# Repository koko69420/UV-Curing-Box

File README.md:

# UV PCB Curing Box

A dedicated, safety-interlocked UV exposure and resin curing chamber controller powered by the ultra-low-cost WCH CH32V003 RISC-V microcontroller, featuring a 4x4 matrix keypad, a 4-digit TM1637 7-segment display, software PWM brightness control, and custom KiCad hardware.

---

## Features

- **RISC-V Microcontroller Core**:
  - Implemented on the WCH CH32V003A4M6 (QingKe 32-bit RISC-V2A core @ 48 MHz, 16 KB Flash, 2 KB SRAM).
  - Built with the PlatformIO Community CH32V Arduino core (`ch32v003fun` HAL).
- **Fail-Safe UV Safety Interlocking**:
  - The high-power UV LED MOSFET (pin A2) is strictly energized ONLY during the active `RUNNING` state.
  - Transitions to `BOOT`, `IDLE`, `READY`, `PAUSED`, or `FINISHED` instantly and continuously force the gate LOW.
- **Dual Timing Modes**:
  - **Timer Mode**: Countdown timer with customizable duration (capped at 8:00 minutes) and automated shutoff.
  - **Stopwatch Mode**: Elapsed time counter with live LED toggling.
- **Fast Presets & Matrix Keypad Input**:
  - 4x4 matrix keypad interface for direct numeric entry, pause/resume, and reset.
  - One-touch curing duration presets:
    - **A**: 1:00 min
    - **B**: 1:30 min
    - **C**: 2:00 min
    - **D**: 3:00 min
  - On-the-fly cycle extension (`#` button adds +5 seconds, clamped to 8:00).
- **PWM Exposure Brightness Regulation**:
  - 50 Hz sampled software PWM (0–100%) designed to eliminate flicker and ensure accurate optical dose delivery.
  - Dedicated on-screen brightness tuning menu (`b 0` to `b100`).
- **Telemetry & Status Display**:
  - TM1637 4-digit 7-segment display showing MM:SS with blinking colon indicators during exposure.
- **Custom Hardware & PCB**:
  - Designed in KiCad with full schematics, PCB routing, 3D step models, and vector silkscreens.

---

## Hardware Specification

### Components & Microcontroller
- **MCU**: WCH CH32V003A4M6 (TSSOP-20).
- **Display**: TM1637 4-digit 0.36" / 0.56" 7-segment clock display module.
- **Keypad**: 4x4 tactile matrix keypad.
- **Switching MOSFET**: N-Channel Power MOSFET (low-side switch on A2 driving 395nm/405nm UV LED arrays).
- **Power Input**: 12V DC input for LED strings with onboard 5V / 3.3V LDO regulation for logic.

---

## Hardware Prototype & Visual Design

### Live Hardware Prototype
Below is the operational controller prototype executing a countdown exposure on the TM1637 4-digit display:

### Electrical Schematic

### PCB Board Layout & Copper Routing

| Complete Board Layout | Top Copper Layer (`F_Cu`) | Bottom Copper Layer (`B_Cu`) |
| :---: | :---: | :---: |
|  |  |  |

---

### Pinout Mapping

| Function | Pin Name | Direction | Description |
| :--- | :--- | :--- | :--- |
| **Keypad Row 1** | C1 | Output | Matrix row scan line 1 |
| **Keypad Row 2** | C2 | Output | Matrix row scan line 2 |
| **Keypad Row 3** | C3 | Output | Matrix row scan line 3 |
| **Keypad Row 4** | C4 | Output | Matrix row scan line 4 |
| **Keypad Col 1** | C6 | Input (Pullup)| Matrix column sense line 1 |
| **Keypad Col 2** | C7 | Input (Pullup)| Matrix column sense line 2 |
| **Keypad Col 3** | D4 | Input (Pullup)| Matrix column sense line 3 |
| **Keypad Col 4** | D5 | Input (Pullup)| Matrix column sense line 4 |
| **TM1637 CLK** | D6 | Output | Display serial clock |
| **TM1637 DIO** | A1 | Bidirectional| Display serial data line |
| **UV MOSFET Gate**| A2 | Output | Low-side power gate driver (PWM) |

---

## State Machine

```mermaid
stateDiagram-v2
    [*] --> BOOT
    BOOT --> IDLE: Initialization Complete
    IDLE --> READY: Digit Entry or Preset (A-D)
    READY --> RUNNING: Press '#' (Start)
    RUNNING --> PAUSED: Press '*' (Pause)
    PAUSED --> RUNNING: Press '#' (Resume)
    PAUSED --> IDLE: Press '*' (Reset to Zero)
    RUNNING --> FINISHED: Time Reaches 0:00 (Timer) or 8:00 (Stopwatch)
    FINISHED --> IDLE: 5s Auto-timeout or Any Key
```

---

## Project Structure

```text
UV-Curing-Box/
├── Programs/                         # PlatformIO firmware project
│   ├── platformio.ini                # CH32V003 target configuration
│   └── src/
│       └── main.cpp                  # Complete non-blocking state machine & firmware
├── Schematic.pdf                     # Schematic diagram export
├── UV_curing_box.kicad_sch           # KiCad schematic
├── UV_curing_box.kicad_pcb           # KiCad PCB board layout
├── MCU_WCH_CH32V003xxx6.kicad_sym   # Custom CH32V003 symbol library
├── led_string.kicad_sch              # UV LED array layout
├── UV_curing_box.svg                 # Scalable vector graphics board plot
├── .gitignore                        # Git ignore rules
└── README.md                         # Project documentation
```

---

## Firmware Compilation & Flashing

### Using PlatformIO (VS Code / CLI)
1. Install [PlatformIO Core](https://platformio.org/) and the Community CH32V platform:
   ```bash
   cd Programs
   pio run
   ```
2. Connect a **WCH-LinkE** programmer to the single-wire debug interface (SWDIO on pin D1, GND, 3V3).
3. Upload firmware:
   ```bash
   pio run --target upload
   ```

---

## License

Open hardware and embedded firmware. All rights reserved by the author.

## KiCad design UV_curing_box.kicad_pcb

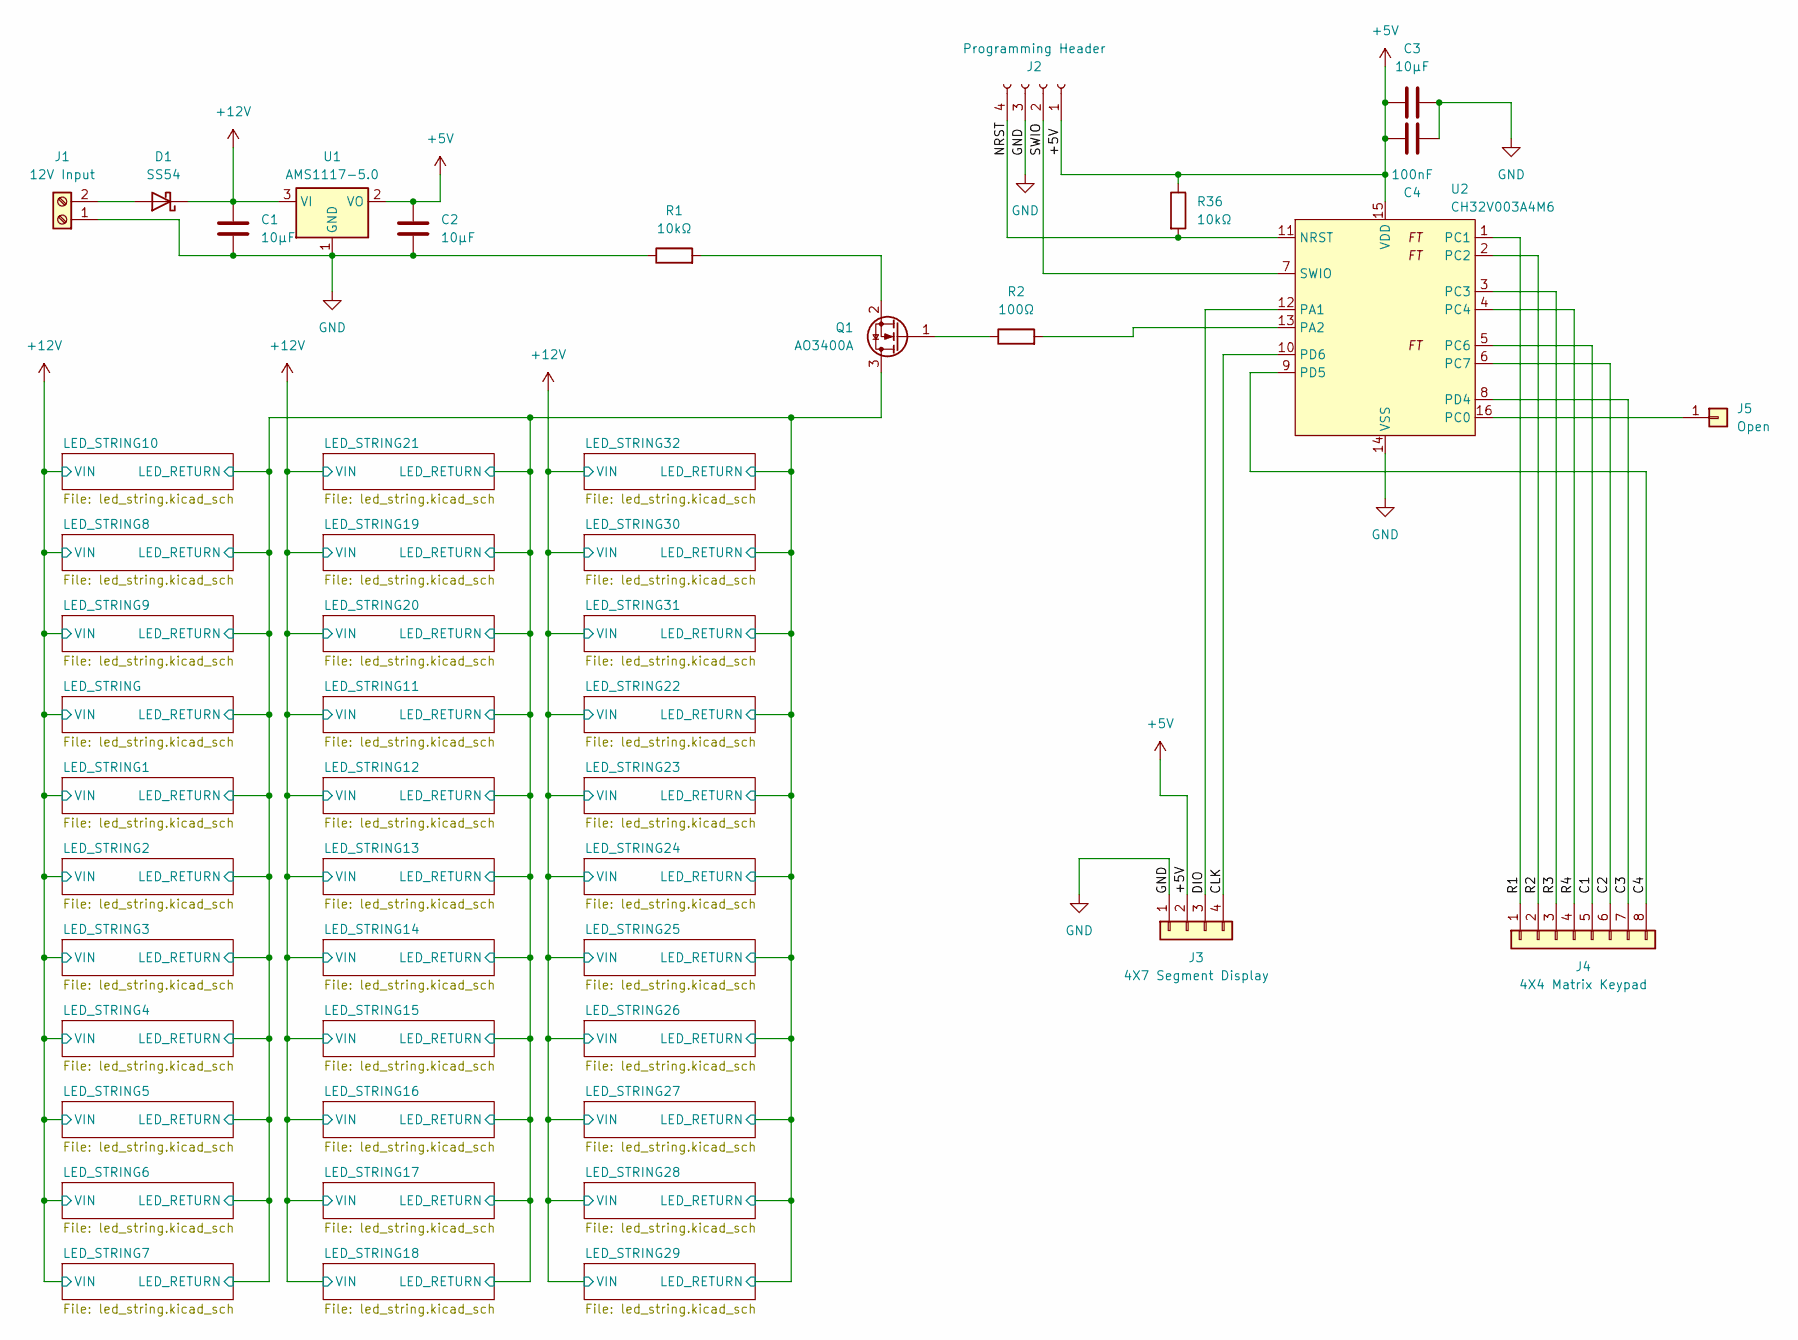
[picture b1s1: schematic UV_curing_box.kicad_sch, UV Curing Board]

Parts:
C1, C2, C3: 10µF; C_1206_3216Metric_Pad1.33x1.80mm_HandSolder
C4: 100nF; C_1206_3216Metric_Pad1.33x1.80mm_HandSolder
D1: SS54; D_SMA_Handsoldering
J1: 12V Input; TerminalBlock_MaiXu_MX126-5.0-02P_1x02_P5.00mm
J2: Programming Header; PinSocket_1x04_P2.54mm_Vertical
J3: 4X7 Segment Display; smd_conn_1x04_2.54
J4: 4X4 Matrix Keypad; smd_conn_1x08_2.54
J5: Open; SolderWirePad_1x01_SMD_1.5x3mm
Q1: AO3400A; SOT-23
R1, R36: 10kΩ; R_1206_3216Metric_Pad1.30x1.75mm_HandSolder
R2: 100Ω; R_1206_3216Metric_Pad1.30x1.75mm_HandSolder
U1: AMS1117-5.0; SOT-223-3_TabPin2
U2: CH32V003A4M6; SO-16_3.9x9.9mm_P1.27mm

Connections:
+5V: C2.1, C3.1, C4.1, J2.1, J3.2, R36.1, U1.2 (VO), U2.15 (VDD)
+12V: C1.1, D1.1 (K), U1.3 (VI); also elsewhere on the board
/C1: J4.5, U2.5 (PC6)
/C2: J4.6, U2.6 (PC7)
/C3: J4.7, U2.8 (PD4)
/C4: J4.8, U2.9 (UART_TX)
/CLK: J3.4, U2.10 (UART_RX)
/DIO: J3.3, U2.12 (OSCI)
/LED_STRING/LED_RETURN: Q1.3 (D); also elsewhere on the board
/NRST: J2.4, R36.2, U2.11 (NRST)
/R1: J4.1, U2.1 (PC1)
/R2: J4.2, U2.2 (PC2)
/R3: J4.3, U2.3 (PC3)
/R4: J4.4, U2.4 (PC4)
/SWIO: J2.2, U2.7 (SWIO)
GND: C1.2, C2.2, C3.2, C4.2, J1.1, J2.3, J3.1, R1.1, U1.1 (GND), U2.14 (VSS)
unnamed: D1.2 (A), J1.2
unnamed: J5.1, U2.16 (PC0)
unnamed: Q1.1 (G), R2.1
unnamed: Q1.2 (S), R1.2
unnamed: R2.2, U2.13 (OSCO)

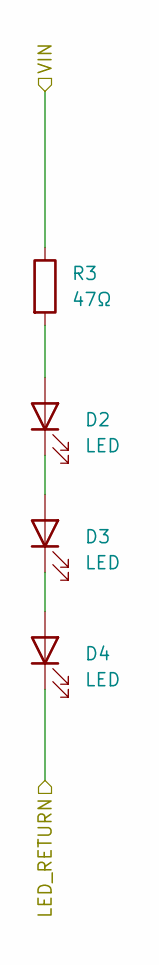
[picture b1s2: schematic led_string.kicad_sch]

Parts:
D2, D3, D4: LED; LED_PLCC_2835_Handsoldering
R3: 47Ω; R_1206_3216Metric_Pad1.30x1.75mm_HandSolder

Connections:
+12V: R3.1; also elsewhere on the board
/LED_STRING/LED_RETURN: D4.1 (K); also elsewhere on the board
unnamed: D2.2 (A), R3.2
unnamed: D2.1 (K), D3.2 (A)
unnamed: D3.1 (K), D4.2 (A)

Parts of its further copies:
D5, D6, D7, D8, D9, D10, D11, D12, D13, D14, D15, D16, D17, D18, D19, D20, D21, D22, D23, D24, D25, D26, D27, D28, D29, D30, D31, D32, D33, D34, D35, D36, D37, D38, D39, D40, D41, D42, D43, D44, D45, D46, D47, D48, D49, D50, D51, D52, D53, D54, D55, D56, D57, D58, D59, D60, D61, D62, D63, D64, D65, D66, D67, D68, D69, D70, D71, D72, D73, D74, D75, D76, D77, D78, D79, D80, D81, D82, D83, D84, D85, D86, D87, D88, D89, D90, D91, D92, D93, D94, D95, D96, D97, D98, D99, D100: LED; LED_PLCC_2835_Handsoldering
R4, R5, R6, R7, R8, R9, R10, R11, R12, R13, R14, R15, R16, R17, R18, R19, R20, R21, R22, R23, R24, R25, R26, R27, R28, R29, R30, R31, R32, R33, R34, R35: 47Ω; R_1206_3216Metric_Pad1.30x1.75mm_HandSolder

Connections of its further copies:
+12V: R4.1, R5.1, R6.1, R7.1, R8.1, R9.1, R10.1, R11.1, R12.1, R13.1, R14.1, R15.1, R16.1, R17.1, R18.1, R19.1, R20.1, R21.1, R22.1, R23.1, R24.1, R25.1, R26.1, R27.1, R28.1, R29.1, R30.1, R31.1, R32.1, R33.1, R34.1, R35.1; also elsewhere on the board
/LED_STRING/LED_RETURN: D7.1 (K), D10.1 (K), D13.1 (K), D16.1 (K), D19.1 (K), D22.1 (K), D25.1 (K), D28.1 (K), D31.1 (K), D34.1 (K), D37.1 (K), D40.1 (K), D43.1 (K), D46.1 (K), D49.1 (K), D52.1 (K), D55.1 (K), D58.1 (K), D61.1 (K), D64.1 (K), D67.1 (K), D70.1 (K), D73.1 (K), D76.1 (K), D79.1 (K), D82.1 (K), D85.1 (K), D88.1 (K), D91.1 (K), D94.1 (K), D97.1 (K), D100.1 (K); also elsewhere on the board
unnamed: D5.2 (A), R4.2
unnamed: D5.1 (K), D6.2 (A)
unnamed: D6.1 (K), D7.2 (A)
unnamed: D8.2 (A), R5.2
unnamed: D8.1 (K), D9.2 (A)
unnamed: D9.1 (K), D10.2 (A)
unnamed: D11.2 (A), R6.2
unnamed: D11.1 (K), D12.2 (A)
unnamed: D12.1 (K), D13.2 (A)
unnamed: D14.2 (A), R7.2
unnamed: D14.1 (K), D15.2 (A)
unnamed: D15.1 (K), D16.2 (A)
unnamed: D17.2 (A), R8.2
unnamed: D17.1 (K), D18.2 (A)
unnamed: D18.1 (K), D19.2 (A)
unnamed: D20.2 (A), R9.2
unnamed: D20.1 (K), D21.2 (A)
unnamed: D21.1 (K), D22.2 (A)
unnamed: D23.2 (A), R10.2
unnamed: D23.1 (K), D24.2 (A)
unnamed: D24.1 (K), D25.2 (A)
unnamed: D26.2 (A), R11.2
unnamed: D26.1 (K), D27.2 (A)
unnamed: D27.1 (K), D28.2 (A)
unnamed: D29.2 (A), R12.2
unnamed: D29.1 (K), D30.2 (A)
unnamed: D30.1 (K), D31.2 (A)
unnamed: D32.2 (A), R13.2
unnamed: D32.1 (K), D33.2 (A)
unnamed: D33.1 (K), D34.2 (A)
unnamed: D35.2 (A), R14.2
unnamed: D35.1 (K), D36.2 (A)
unnamed: D36.1 (K), D37.2 (A)
unnamed: D38.2 (A), R15.2
unnamed: D38.1 (K), D39.2 (A)
unnamed: D39.1 (K), D40.2 (A)
unnamed: D41.2 (A), R16.2
unnamed: D41.1 (K), D42.2 (A)
unnamed: D42.1 (K), D43.2 (A)
unnamed: D44.2 (A), R17.2
unnamed: D44.1 (K), D45.2 (A)
unnamed: D45.1 (K), D46.2 (A)
unnamed: D47.2 (A), R18.2
unnamed: D47.1 (K), D48.2 (A)
unnamed: D48.1 (K), D49.2 (A)
unnamed: D50.2 (A), R19.2
unnamed: D50.1 (K), D51.2 (A)
unnamed: D51.1 (K), D52.2 (A)
unnamed: D53.2 (A), R20.2
unnamed: D53.1 (K), D54.2 (A)
unnamed: D54.1 (K), D55.2 (A)
unnamed: D56.2 (A), R21.2
unnamed: D56.1 (K), D57.2 (A)
unnamed: D57.1 (K), D58.2 (A)
unnamed: D59.2 (A), R22.2
unnamed: D59.1 (K), D60.2 (A)
unnamed: D60.1 (K), D61.2 (A)
unnamed: D62.2 (A), R23.2
unnamed: D62.1 (K), D63.2 (A)
unnamed: D63.1 (K), D64.2 (A)
unnamed: D65.2 (A), R24.2
unnamed: D65.1 (K), D66.2 (A)
unnamed: D66.1 (K), D67.2 (A)
unnamed: D68.2 (A), R25.2
unnamed: D68.1 (K), D69.2 (A)
unnamed: D69.1 (K), D70.2 (A)
unnamed: D71.2 (A), R26.2
unnamed: D71.1 (K), D72.2 (A)
unnamed: D72.1 (K), D73.2 (A)
unnamed: D74.2 (A), R27.2
unnamed: D74.1 (K), D75.2 (A)
unnamed: D75.1 (K), D76.2 (A)
unnamed: D77.2 (A), R28.2
unnamed: D77.1 (K), D78.2 (A)
unnamed: D78.1 (K), D79.2 (A)
unnamed: D80.2 (A), R29.2
unnamed: D80.1 (K), D81.2 (A)
unnamed: D81.1 (K), D82.2 (A)
unnamed: D83.2 (A), R30.2
unnamed: D83.1 (K), D84.2 (A)
unnamed: D84.1 (K), D85.2 (A)
unnamed: D86.2 (A), R31.2
unnamed: D86.1 (K), D87.2 (A)
unnamed: D87.1 (K), D88.2 (A)
unnamed: D89.2 (A), R32.2
unnamed: D89.1 (K), D90.2 (A)
unnamed: D90.1 (K), D91.2 (A)
unnamed: D92.2 (A), R33.2
unnamed: D92.1 (K), D93.2 (A)
unnamed: D93.1 (K), D94.2 (A)
unnamed: D95.2 (A), R34.2
unnamed: D95.1 (K), D96.2 (A)
unnamed: D96.1 (K), D97.2 (A)
unnamed: D98.2 (A), R35.2
unnamed: D98.1 (K), D99.2 (A)
unnamed: D99.1 (K), D100.2 (A)

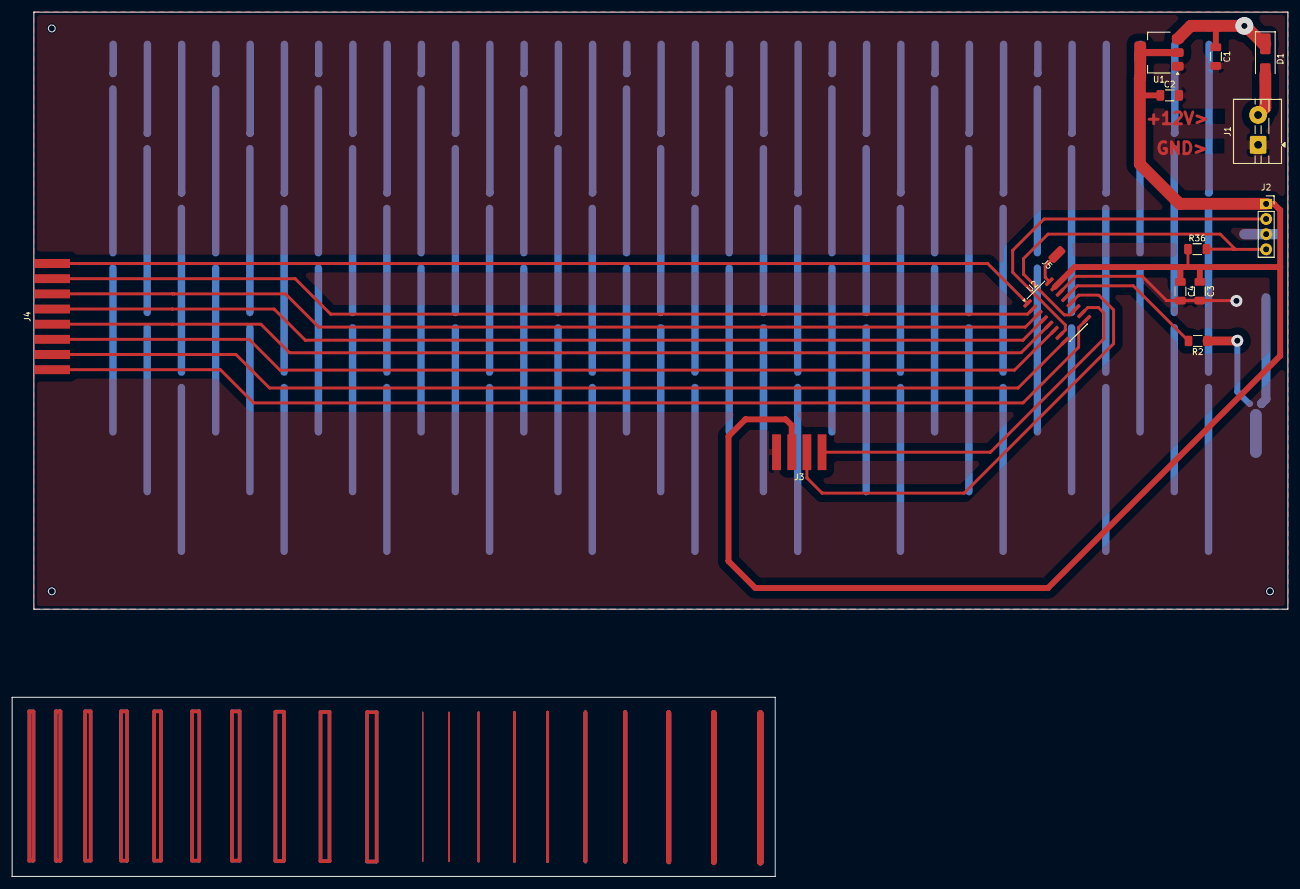
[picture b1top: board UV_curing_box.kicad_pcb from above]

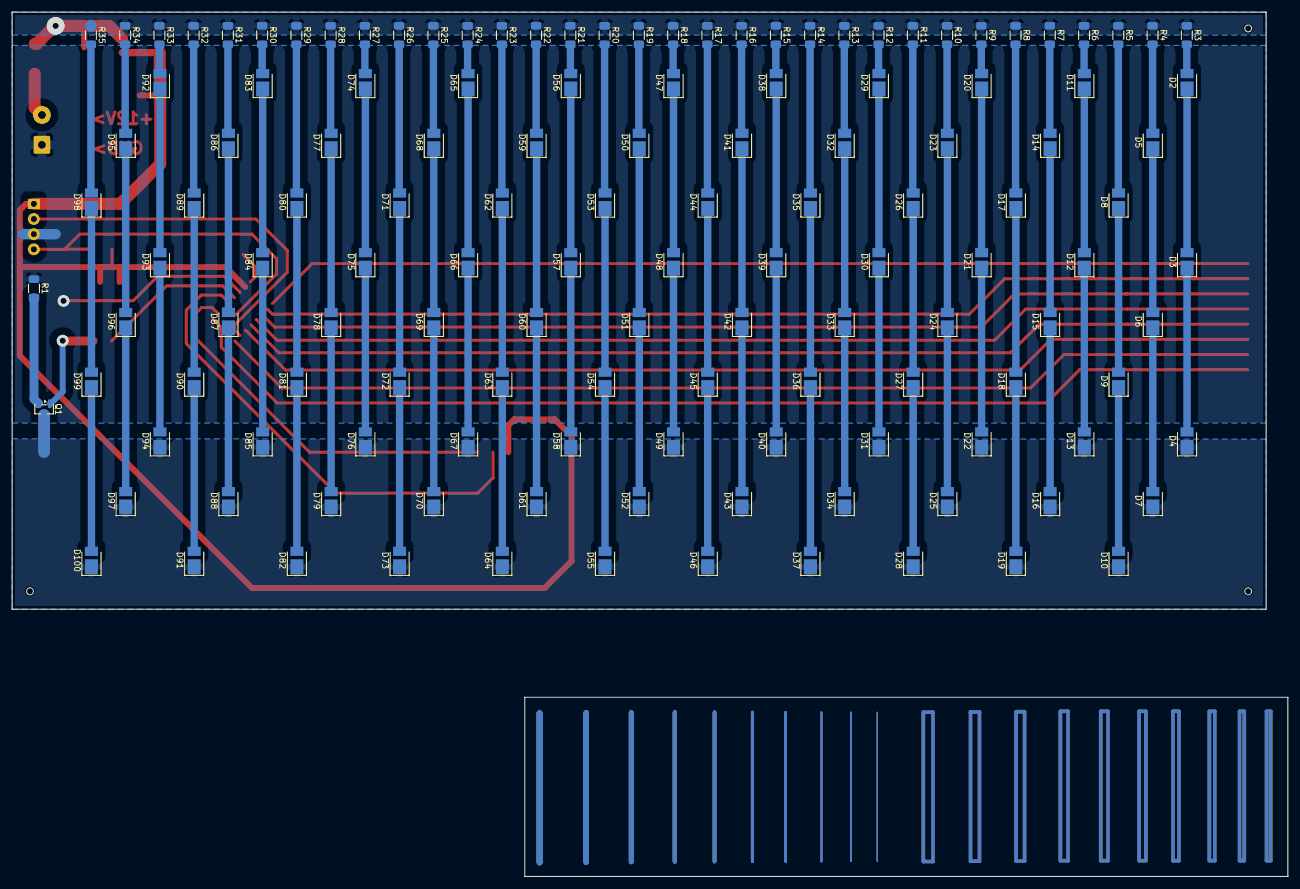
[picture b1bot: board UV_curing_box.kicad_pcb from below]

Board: 2 copper layers, 210.0 x 100.0 mm, 148 parts (134 on the bottom side), 120 nets.
